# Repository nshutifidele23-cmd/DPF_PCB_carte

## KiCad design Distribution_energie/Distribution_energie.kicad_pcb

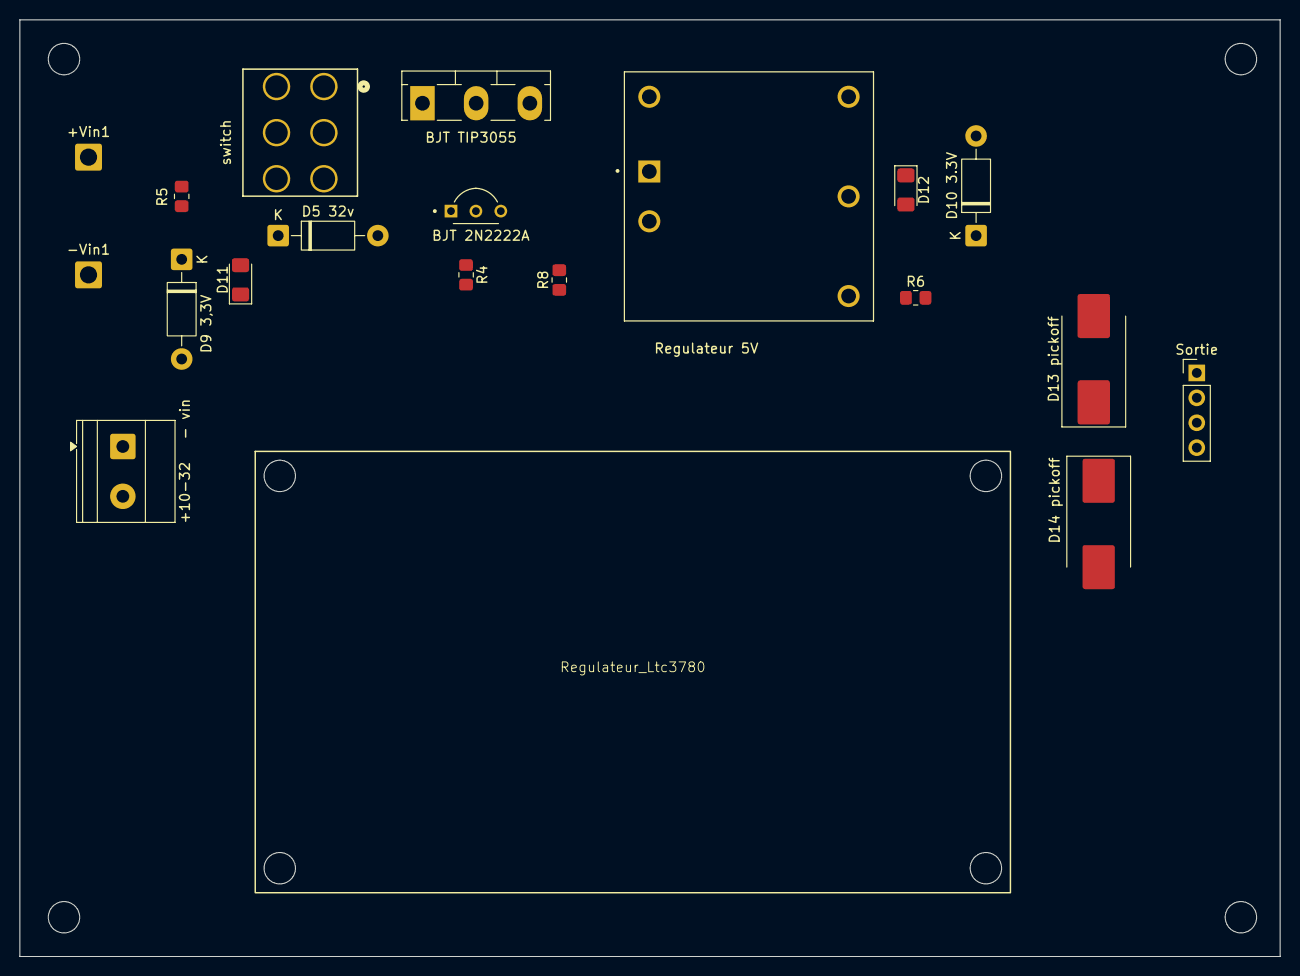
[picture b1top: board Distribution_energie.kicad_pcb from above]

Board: 2 copper layers, 128.5 x 95.5 mm, 20 parts (0 on the bottom side), 13 nets, no tracks yet.

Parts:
+10-32   - vin   : +10-32V; TerminalBlock_Phoenix_MKDS-1,5-2-5.08_1x02_P5.08mm_Horizont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
+Vin1: +vin_10v_35V; SolderWire-1sqmm_1x01_D1.4mm_OD2.7mm
-Vin1: -Vin_10v_35V; SolderWire-1sqmm_1x01_D1.4mm_OD2.7mm
BJT 2N2222A: 2N2222A; TO92254P470H750-3
BJT TIP3055: TIP3055; TO-218-3_Vertical
D5 32v: 1N4752A; D_DO-41_SOD81_P10.16mm_Horizontal
D9 3,3V, D10 3.3V: 1N4728A; D_DO-41_SOD81_P10.16mm_Horizontal
D11: Led rouge; LED_1206_3216Metric_Pad1.42x1.75mm_HandSolder
D12: Led vert; LED_1206_3216Metric_Pad1.42x1.75mm_HandSolder
D13 pickoff, D14 pickoff: D; D_SMC_Handsoldering
R4, R6: 1K; R_0805_2012Metric_Pad1.20x1.40mm_HandSolder
R5: 4.7k; R_0805_2012Metric_Pad1.20x1.40mm_HandSolder
R8: 4.7K; R_0805_2012Metric_Pad1.20x1.40mm_HandSolder
Regulateur 5V: DQD6-24-S5; CONV_DQD6-24-S5
Regulateur_Ltc3780: Regulateur LTC3780
Sortie: Conn_01x04; PinHeader_1x04_P2.54mm_Vertical
switch: 7201SYCQE; SW6_7201SYCQE_CNK

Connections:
0V vin-: +10-32 - vin.1, -Vin1.1 (Pin_1_1), D5 32v.2 (A), D9 3,3V.2 (A), D11.1 (K), R8.2, Regulateur 5V.1 (-VIN)
10-32V vin+: +10-32 - vin.2, BJT TIP3055.3 (E), R8.1, Regulateur 5V.2 (+VIN)
10-35V vin+: +Vin1.1 (Pin_1_1), switch.4
+5V: R6.2, Regulateur 5V.3 (+VOUT), Sortie.4
+24V_A: D13 pickoff.2 (A), Sortie.1
+24V_B: D13 pickoff.1 (K), D14 pickoff.1 (K), Sortie.2
GNDPWR: D10 3.3V.2 (A), D12.1 (K), D14 pickoff.2 (A), Regulateur 5V.5 (GND), Sortie.3
unnamed: BJT 2N2222A.2, D5 32v.1 (K), R4.1
unnamed: D10 3.3V.1 (K), D12.2 (A), R6.1
unnamed: D9 3,3V.1 (K), D11.2 (A), R5.1
unnamed: BJT 2N2222A.1, BJT TIP3055.1 (B)
unnamed: BJT 2N2222A.3, BJT TIP3055.2 (C), R4.2, switch.2
unnamed: switch.1, switch.5
